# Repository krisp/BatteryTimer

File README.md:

<pre>
BatteryTimer
============

Arduino Micro-based programmable relay switch with voltage sensing.

Includes serial CLI support for changing initial parameters to user-defined settings.

Theory of operation:
  At initial power up, default settings are saved to EEPROM. Subsequent reboots will 
  read these values. Relay is turned off unless voltage is above VOLTAGE_ON. Initially,
  the firmware remains in a fully on initial state until PD_WAIT seconds elapse. Data 
  received via the CLI resets this timer. After PD_WAIT seconds, the board goes into 
  full powerdown and wakes up every second to sense the input voltage. If the 
  voltage is sensed to be greater than or equal to VOLTAGE_ON, the relay is engaged 
  and powerdown mode is disabled. Once the voltage drops below VOLTAGE_ON, the relay 
  will remain engaged until OFF_WAIT seconds elapse. Should the voltage drop below
  VOLTAGE_LOW at any time, the relay will immediately be disengaged and powerdown mode 
  will be activated.
  
Parameters:
  VOLTAGE_ON  : voltage (float) at which the relay engages. Default: 13.2
  VOLTAGE_LOW : voltage (float) at which the relay is immediately disengaged and 
                powerdown mode activated. Default: 10.8
  OFF_WAIT    : time in seconds for the relay to remain engaged after voltage drops 
                below VOLTAGE_ON. Default: 120 (2 minutes)
  PD_WAIT     : time in seconds to wait initially before entering powerdown mode. 
                This allows the user to connect via CLI before USB is disabled.
				Default: 45 seconds
  VDROP_DETECT: Flag to enable voltage drop detection to reset delay timer (1 or 0)
  VDROP_PCT   : Multiplied by median voltage and then compared to current voltage, 
                if voltage is less it will reset the timer (in-use detect). Default
				value is 0.99 (which is 1% drop or 0.115v at 11.5v)
  
Power consumption:
  Using Arduino Micro (atmega32u4) boards acquired from China via Ebay (with power LED 
  removed), this project has been measured at 240 microamps current draw while in 
  powerdown. Full on current draw with relay engaged is ~70mA, full on current draw with 
  relay open is ~32mA. 

Using the CLI:
  Connect the Arduino Micro board via USB and establish a serial connection at 9600bps 
  within PD_WAIT. Press enter to activate the CLI and reset the PD_WAIT timer. Type
  help for a list of commands and their use. Note that changes to parameters are not
  saved until the "save" command is issued.
  
Voltage drop detection:
  The current voltage is added to an array used to compute the running median voltage
  when the system is in delayed off state. The median voltage is multiplied by VDROP_PCT 
  and compared to the current voltage reading. If the current voltage reading is less 
  than VDROP_PCT*median_voltage, the off timer is reset and the controlled device will
  remain powered on for another OFF_WAIT seconds.
</pre>

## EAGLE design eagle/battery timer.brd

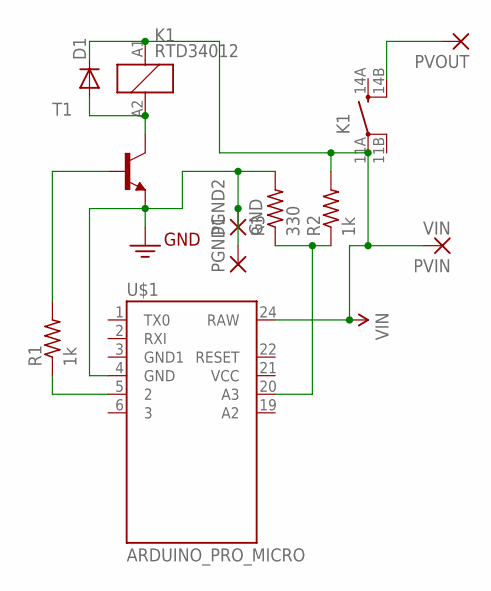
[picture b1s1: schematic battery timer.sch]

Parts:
D1: DIODE-DO-214AC; DO-214AC
K1: RTD34012; RT-N/O16A5
PGND1: SMD5; SMD2,54-5,08
PGND2: GND; SMD2,54-5,08
PVIN: VIN; SMD2,54-5,08
PVOUT: SMD5; SMD2,54-5,08
R1, R2: 1k; R1206
R3: 330; R1206
T1: MMBT4401LT1-NPN-SOT23-BEC; SOT23-BEC
U$1: ARDUINO_PRO_MICRO

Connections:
3.3V: PGND1.1, PGND2.1, R3.2, T1.E, U$1.4 (GND)
unnamed: R2.1, R3.1, U$1.20 (A3)
unnamed: R1.1, U$1.5 (2)
unnamed: D1.A, K1.A2 (2), T1.C
unnamed: R1.2, T1.B
PVOUT: K1.14B (SB), PVOUT.1
VIN: D1.C, K1.11A (PA), K1.A1 (1), PVIN.1, R2.2, U$1.24 (RAW)

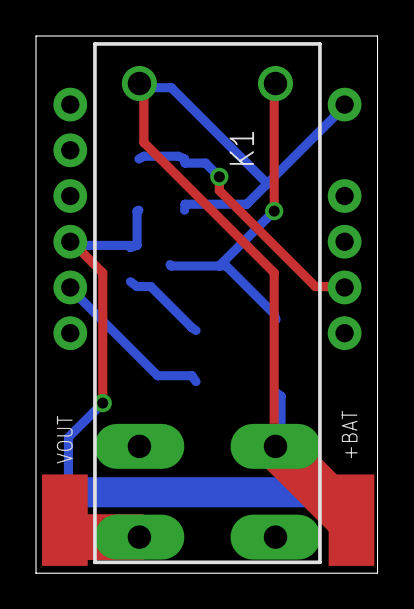
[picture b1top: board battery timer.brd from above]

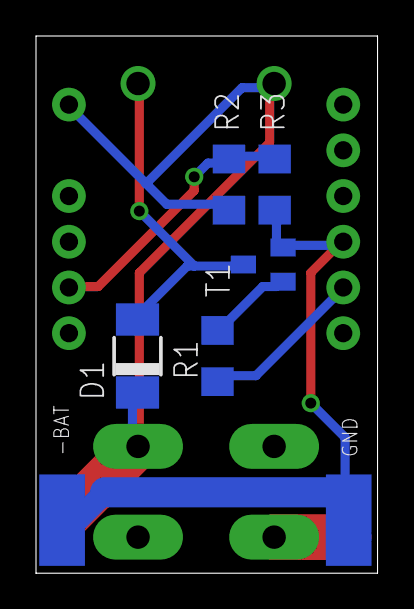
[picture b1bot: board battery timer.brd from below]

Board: 2 copper layers, 19.0 x 29.8 mm, 11 parts (7 on the bottom side), 7 nets.

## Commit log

2014-12-02 Added board files and version 1.0 source
2014-12-02 Move status printing into initialState delay block
    USB is off during power down, so make sure we are in the initial state
    or power down mode is off before trying to print the status.
2014-12-02 Moved parameters to EEPROM and added CLI support
2014-12-04 Added running median and voltage drop detection
2014-12-04 Moved around loop execution measurement and fixed string buffer overflow on param list
2014-12-04 Added VDROP_DETECT param to toggle voltage drop detect

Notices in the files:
parts and their libraries:
SparkFun-Boards: Licensing: CC v3.0 Share-Alike You are welcome to use this library for commercial purposes.
